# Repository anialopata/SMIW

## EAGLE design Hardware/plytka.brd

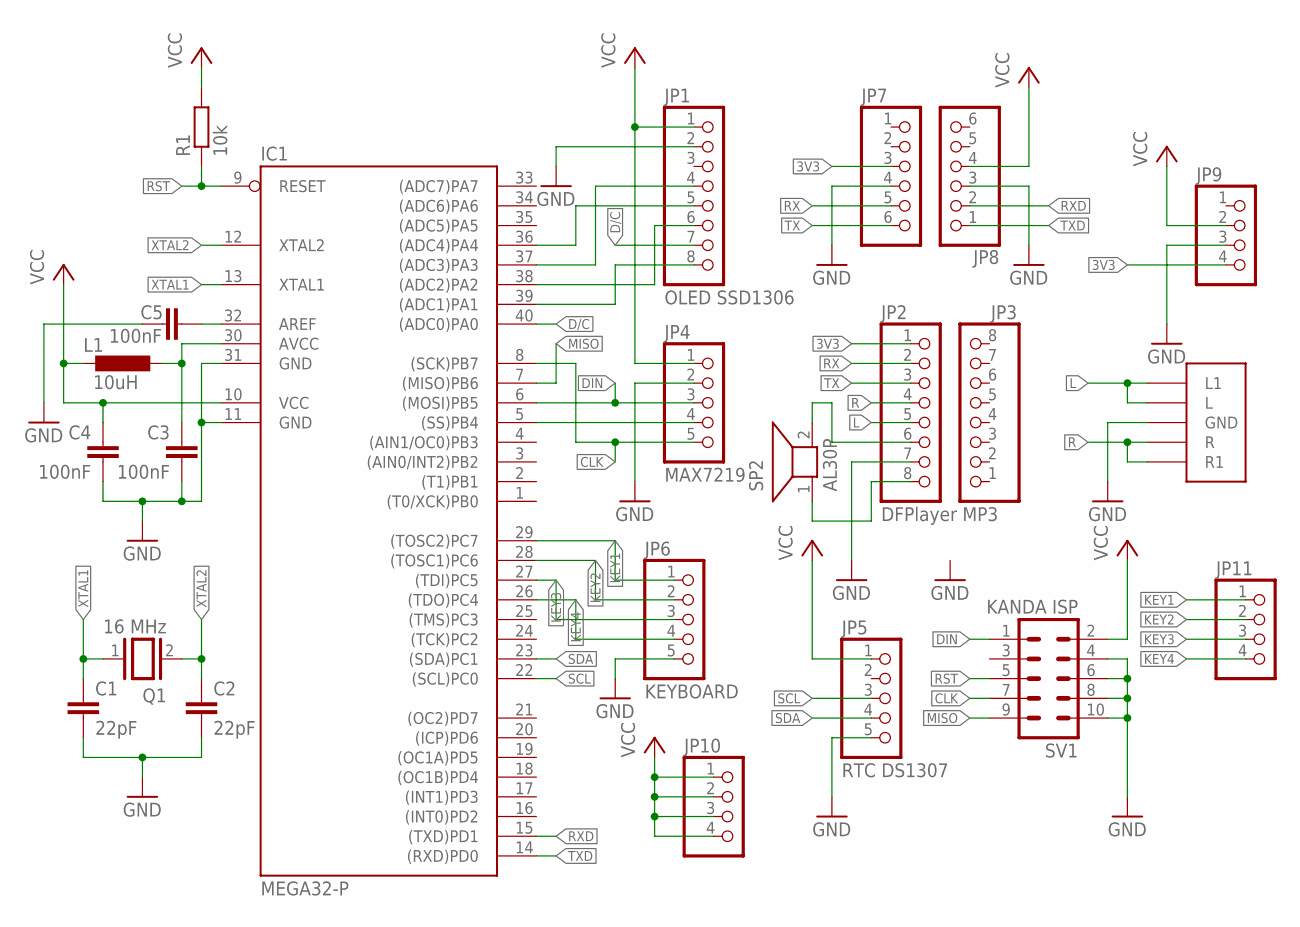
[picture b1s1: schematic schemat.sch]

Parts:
C1, C2: 22pF; C025-025X050
C3, C4, C5: 100nF; C025-025X050
IC1: MEGA32-P; DIL40
JP1: OLED SSD1306; 1X08
JP2: DFPlayer MP3; 1X08
JP3: 1X08
JP4: MAX7219; 1X05
JP5: RTC DS1307; 1X05
JP6: KEYBOARD; 1X05
JP7, JP8: PINHD-1X6; 1X06
JP9, JP10, JP11: PINHD-1X4; 1X04
L1: 10uH; 0204/5
Q1: 16 MHz; QS
R1: 10k; 0207/7
SP2: AL30P
SV1: KANDA ISP; ML10
U$1: STEREO_D; STEREO_P

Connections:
3V3: JP2.1, JP7.3, JP9.4
AVCC: C3.1, IC1.30 (AVCC), L1.1
CLK: IC1.8 ((SCK)PB7), JP4.5, SV1.7
CS: IC1.5 ((SS)PB4), JP4.4
D/C: IC1.40 ((ADC0)PA0), JP1.7
DIN: IC1.6 ((MOSI)PB5), JP4.3, SV1.1
GND: C1.2, C2.2, C3.2, C4.2, C5.2, IC1.11 (GND), IC1.31 (GND), JP1.2, JP2.7, JP4.2, JP5.5, JP6.5, JP7.4, JP8.3, JP9.3, SV1.4, SV1.6, SV1.8, SV1.10, U$1.GND
KEY1: IC1.29 ((TOSC2)PC7), JP6.1, JP11.1
KEY2: IC1.28 ((TOSC1)PC6), JP6.2, JP11.2
KEY3: IC1.27 ((TDI)PC5), JP6.3, JP11.3
KEY4: IC1.26 ((TDO)PC4), JP6.4, JP11.4
L: JP2.5, U$1.L_A (L1), U$1.L_B (L)
MISO: IC1.7 ((MISO)PB6), SV1.9
unnamed: C5.1, IC1.32 (AREF)
unnamed: JP2.8, SP2.1
unnamed: JP2.6, SP2.2
unnamed: IC1.37 ((ADC3)PA3), JP1.4
unnamed: IC1.38 ((ADC2)PA2), JP1.6
unnamed: IC1.36 ((ADC4)PA4), JP1.5
R: JP2.4, U$1.R_A (R1), U$1.R_B (R)
RST: IC1.9 (RESET), R1.1, SV1.5
RST_SSD: IC1.39 ((ADC1)PA1), JP1.8
RX: JP2.2, JP7.5
RXD: IC1.15 ((TXD)PD1), JP8.2
SCL: IC1.22 ((SCL)PC0), JP5.3
SDA: IC1.23 ((SDA)PC1), JP5.4
TX: JP2.3, JP7.6
TXD: IC1.14 ((RXD)PD0), JP8.1
VCC: C4.1, IC1.10 (VCC), JP1.1, JP4.1, JP5.1, JP8.4, JP9.2, JP10.1, JP10.2, JP10.3, JP10.4, L1.2, R1.2, SV1.2
XTAL1: C1.1, IC1.13 (XTAL1), Q1.1
XTAL2: C2.1, IC1.12 (XTAL2), Q1.2

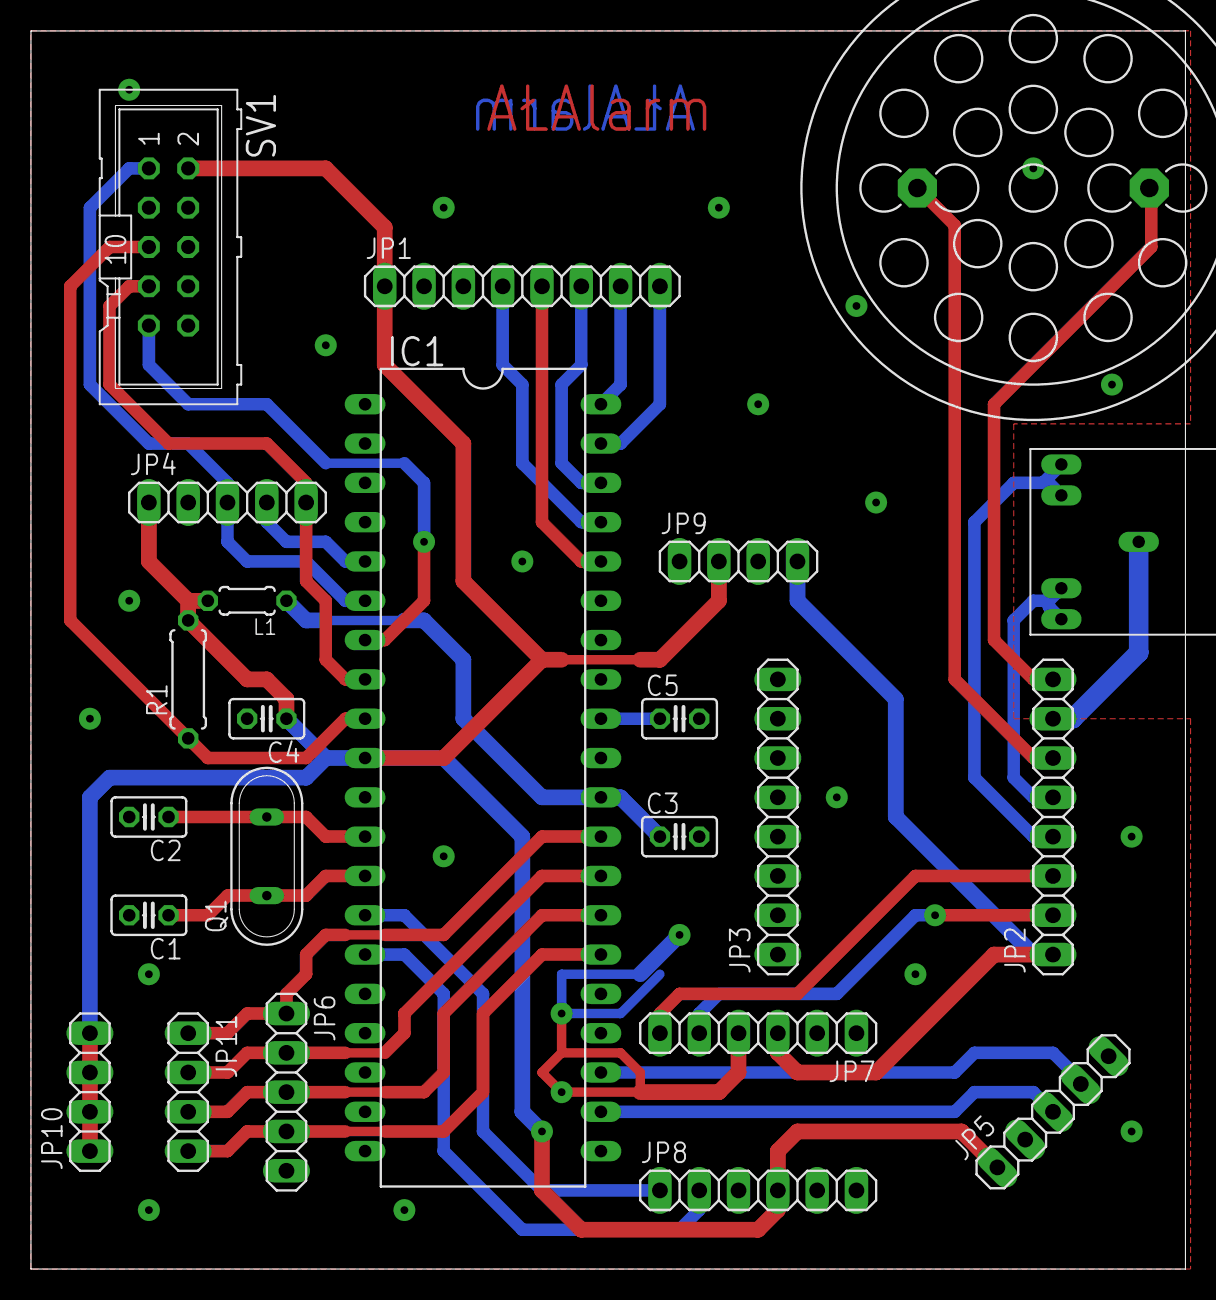
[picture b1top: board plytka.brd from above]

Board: 2 copper layers, 74.6 x 80.0 mm, 23 parts (0 on the bottom side), 31 nets.

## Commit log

2018-09-09 Budzik - projekt
